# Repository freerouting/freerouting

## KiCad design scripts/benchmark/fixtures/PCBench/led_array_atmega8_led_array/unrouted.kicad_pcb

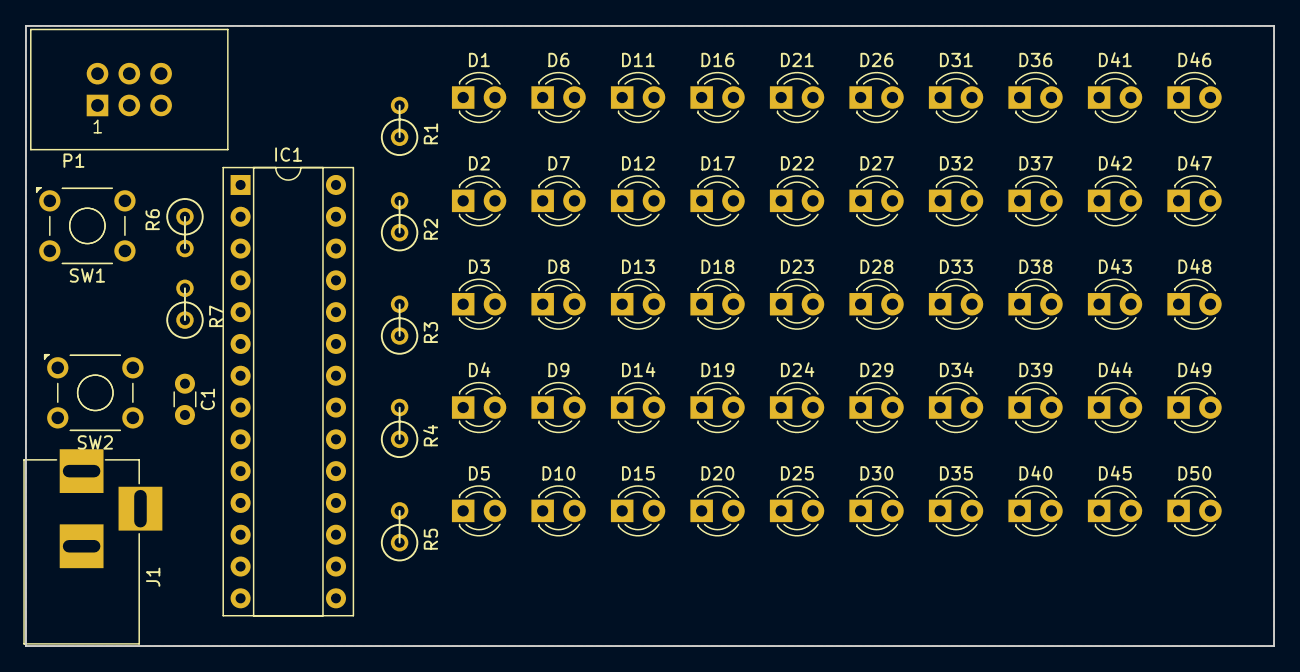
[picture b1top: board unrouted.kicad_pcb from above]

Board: 2 copper layers, 99.7 x 49.5 mm, 63 parts (0 on the bottom side), 25 nets, no tracks yet.

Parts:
C1: 0.1uF; C_Disc_D3.0mm_W1.6mm_P2.50mm
D1, D2, D3, D4, D5, D6, D7, D8, D9, D10, D11, D12, D13, D14, D15, D16, D17, D18, D19, D20, D21, D22, D23, D24, D25, D26, D27, D28, D29, D30, D31, D32, D33, D34, D35, D36, D37, D38, D39, D40, D41, D42, D43, D44, D45, D46, D47, D48, D49, D50: LED; LED_D3.0mm
IC1: ATMEGA8-P; DIP-28_W7.62mm_Socket
J1: BARREL_JACK
P1: ICSP; IDC_Header_Straight_6pins
R1, R2, R3, R4, R5: 220; R1
R6, R7: 1k; R1
SW1: next; SW_TH_Tactile_Omron_B3F-10xx
SW2: prev; SW_TH_Tactile_Omron_B3F-10xx

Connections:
+5V: C1.1, IC1.7, J1.1, P1.2, SW1.1, SW1.3, SW2.1, SW2.3
GND: C1.2, IC1.8, J1.2, J1.3, P1.6, R6.1, R7.1
MISO: D11.1, D12.1, D13.1, D14.1, D15.1, IC1.18, P1.1
MOSI: D16.1, D17.1, D18.1, D19.1, D20.1, IC1.17, P1.4
unnamed: D1.2, D6.2, D11.2, D16.2, D21.2, D26.2, D31.2, D36.2, D41.2, D46.2, R1.2
unnamed: D5.2, D10.2, D15.2, D20.2, D25.2, D30.2, D35.2, D40.2, D45.2, D50.2, R5.2
unnamed: D2.2, D7.2, D12.2, D17.2, D22.2, D27.2, D32.2, D37.2, D42.2, D47.2, R2.2
unnamed: D3.2, D8.2, D13.2, D18.2, D23.2, D28.2, D33.2, D38.2, D43.2, D48.2, R3.2
unnamed: D4.2, D9.2, D14.2, D19.2, D24.2, D29.2, D34.2, D39.2, D44.2, D49.2, R4.2
RST: IC1.1, P1.5
SCK: D6.1, D7.1, D8.1, D9.1, D10.1, IC1.19, P1.3
back: IC1.5, R7.2, SW2.2, SW2.4
col1: D1.1, D2.1, D3.1, D4.1, D5.1, IC1.23
col5: D21.1, D22.1, D23.1, D24.1, D25.1, IC1.16
col6: D26.1, D27.1, D28.1, D29.1, D30.1, IC1.15
col7: D31.1, D32.1, D33.1, D34.1, D35.1, IC1.14
col8: D36.1, D37.1, D38.1, D39.1, D40.1, IC1.11
col9: D41.1, D42.1, D43.1, D44.1, D45.1, IC1.12
col10: D46.1, D47.1, D48.1, D49.1, D50.1, IC1.13
forward: IC1.4, R6.2, SW1.2, SW1.4
row1: IC1.28, R1.1
row2: IC1.27, R2.1
row3: IC1.26, R3.1
row4: IC1.25, R4.1
row5: IC1.24, R5.1

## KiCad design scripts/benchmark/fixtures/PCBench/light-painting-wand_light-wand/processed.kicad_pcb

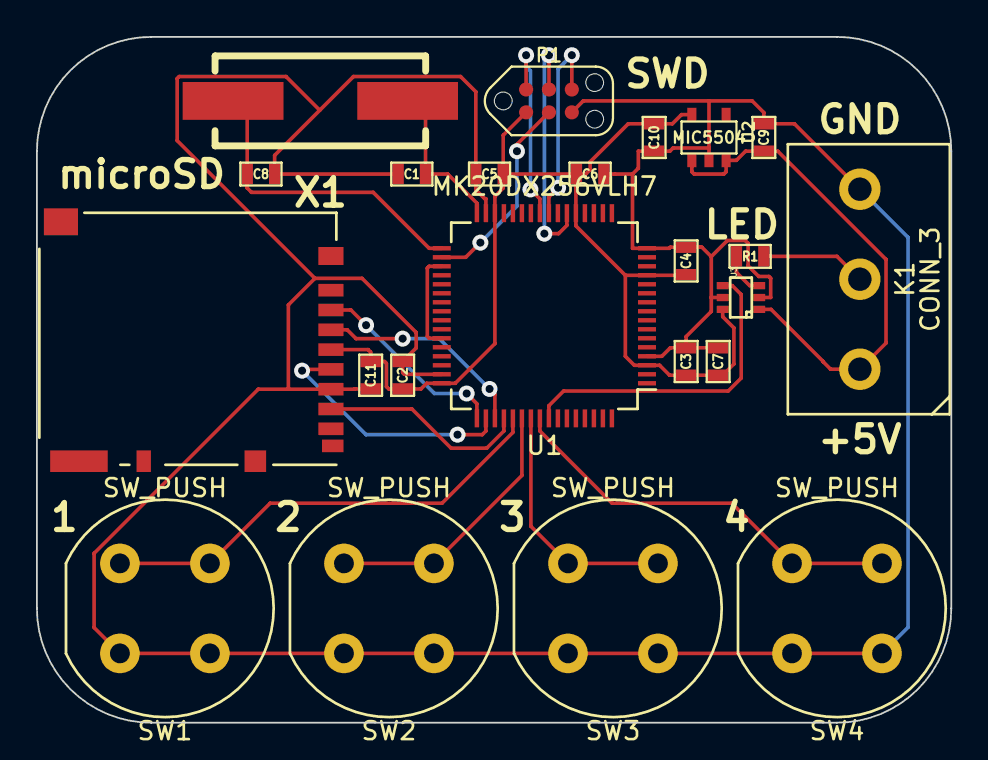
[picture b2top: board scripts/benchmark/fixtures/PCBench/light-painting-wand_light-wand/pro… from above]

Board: 2 copper layers, 50.8 x 38.1 mm, 24 parts (1 on the bottom side), 21 nets.

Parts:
C1, C8: 27pF; SMD-0603
C2, C3, C4, C5, C6, C11: 0.1uF; SMD-0603
C7: 2.2uF; SMD-0603
C9, C10: 1uF; SMD-0603
K1: CONN_3; 1935174
P1: TC2030-CTX; TC2030-NL_SMALL
R1: 68; SMD-0603
SW1, SW2, SW3, SW4: SW_PUSH; D6_SWITCH
SYM: Symbol_OSHW-Logo_SilkScreen_07Jul2012; Symbol_OSHW-Logo_SilkScreen
U1: MK20DX256VLH7; LQFP-64_10x10mm_Pitch0.5mm
U2: MIC5504; SOT-23-5
U3: SN74LVC1T45; sc70-6
U4: MICROSD_SOCKET; DM3BT
X1: 16MHz; Crystal_HC49-SD_SMD

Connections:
+3.3V: C2.1, C3.1, C4.1, C5.1, C6.1, C7.1, C10.1, C11.1, P1.1, U1.3, U1.13, U1.21, U1.30, U1.48, U2.5, U3.6, U4.4
+5V: C9.1, K1.1, U2.1, U2.3, U3.1
/BTN1: SW1.1, U1.53
/BTN2: SW2.1, U1.54
/BTN3: SW3.1, U1.55
/BTN4: SW4.1, U1.56
/CS: U1.49, U4.2
/MISO: U1.52, U4.7
/MOSI: U1.51, U4.3
/RESET: P1.3, U1.34
/SCK: U1.50, U4.5
/SWCLK: P1.4, U1.22
/SWDIO: P1.2, U1.25
/SWO: P1.6, U1.24
/WS2812: R1.2, U3.3
/WS2812_L: U1.57, U3.4
GND: C1.2, C2.2, C3.2, C4.2, C5.2, C6.2, C7.2, C8.2, C9.2, C10.2, C11.2, K1.3, P1.5, SW1.2, SW2.2, SW3.2, SW4.2, U1.4, U1.16, U1.31, U1.47, U2.2, U3.2, U3.5, U4.6
unnamed: C1.1, U1.32, X1.1
unnamed: C8.1, U1.33, X1.2
unnamed: K1.2, R1.1
unnamed: U1.35, U1.43

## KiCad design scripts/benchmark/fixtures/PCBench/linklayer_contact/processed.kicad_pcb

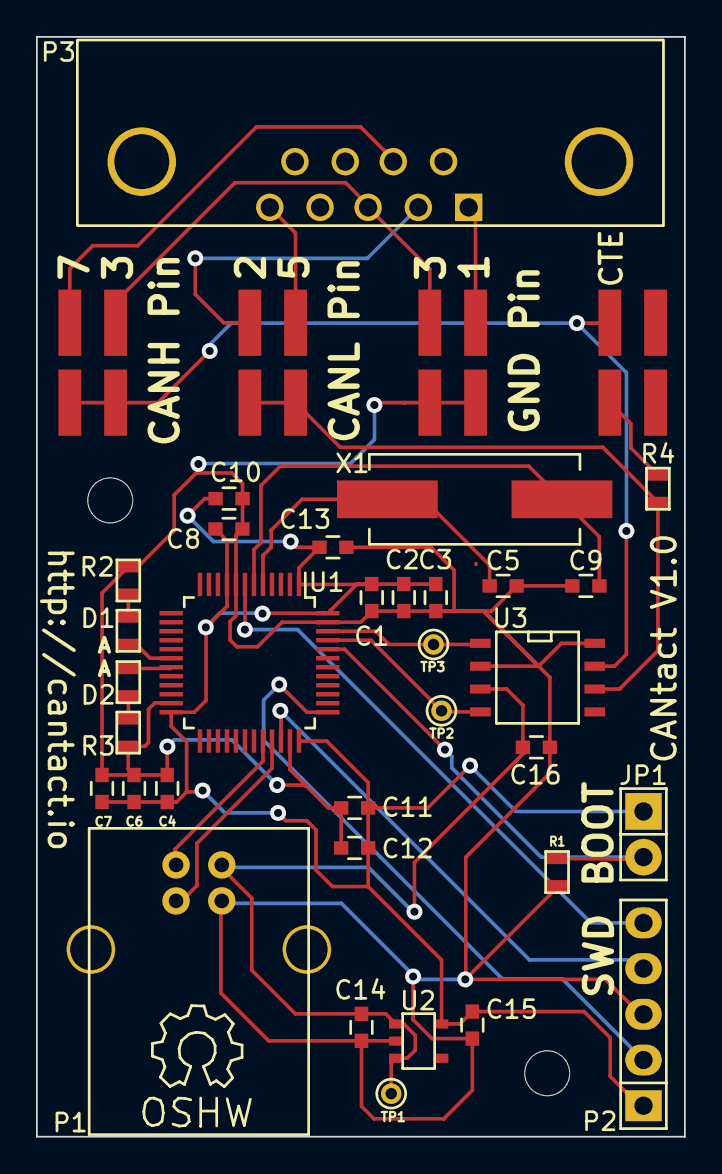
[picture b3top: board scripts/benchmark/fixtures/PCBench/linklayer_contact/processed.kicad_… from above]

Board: 2 copper layers, 36.0 x 61.1 mm, 40 parts (0 on the bottom side), 25 nets.

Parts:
C1, C2, C4, C6, C11, C13, C16: 0.1uF; C_0603
C3, C7, C12: 4.7uF; C_0603
C5, C9: 18pF; C_0603
C8: 10nF; C_0603
C10, C14, C15: 1uF; C_0603
D1, D2: LED; SMD-0603
JP1: Boot Mode; Pin_Header_Straight_1x02
JP2: Term Enable; 0015912040
JP3: CANH Select; 0015912040
JP4: CANL Select; 0015912040
JP5: GND Select; 0015912040
Noname_1, Noname_2: VAL**; MountingHole_2-5mm
P1: USB; USB_B
P2: SWD; Pin_Header_Straight_1x05
P3: DB9; DB9MC
R1: 510; SMD-0603
R2, R3: R; SMD-0603
R4: 120; SMD-0603
SYM: Symbol_OSHW-Logo_SilkScreen_07Jul2012; Symbol_OSHW-Logo_SilkScreen
TP1, TP2, TP3: TST; PINTST
U1: STM32F042C6T6; LQFP-48_7x7mm_Pitch0.5mm
U2: AAT3221; SOT-23-5
U3: MCP2551-I/SN; SOIC-8-N
X1: 16 MHz; Crystal_HC49-SD_SMD

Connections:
+3.3V: C1.1, C2.1, C3.1, C4.1, C6.1, C7.1, C8.1, C10.1, C11.1, C12.1, C13.1, C15.1, JP1.1, P2.1, U1.1, U1.9, U1.24, U1.36, U1.48, U2.5
+5V: C14.1, C16.2, P1.1, TP1.1, U2.1, U2.3, U3.3
/CAN_RX: TP2.1, U1.45, U3.4
/CAN_TX: TP3.1, U1.46, U3.1
/DB9_1: JP5.4, P3.1
/DB9_2: JP4.2, P3.2
/DB9_3: JP3.4, JP5.2, P3.3
/DB9_5: JP4.4, P3.5
/DB9_7: JP3.2, P3.7
/NRST: P2.5, U1.7
/SWCLK: P2.2, U1.37
/SWDIO: P2.4, U1.34
/USB_DM: P1.2, U1.32
/USB_DP: P1.3, U1.33
GND: C1.2, C2.2, C3.2, C4.2, C5.2, C6.2, C7.2, C8.2, C9.2, C10.2, C11.2, C12.2, C13.2, C14.2, C15.2, C16.1, JP5.1, JP5.3, P1.4, P2.3, R1.2, R2.1, R3.1, U1.8, U1.23, U1.35, U1.47, U2.2, U3.2, U3.8
unnamed: C5.1, U1.5, X1.1
unnamed: C9.1, U1.6, X1.2
unnamed: D1.1, U1.18
unnamed: D1.2, R2.2
unnamed: D2.1, U1.19
unnamed: D2.2, R3.2
unnamed: JP1.2, R1.1, U1.44
unnamed: JP2.1, R4.2
unnamed: JP2.2, JP3.1, JP3.3, U3.7
unnamed: JP4.1, JP4.3, R4.1, U3.6

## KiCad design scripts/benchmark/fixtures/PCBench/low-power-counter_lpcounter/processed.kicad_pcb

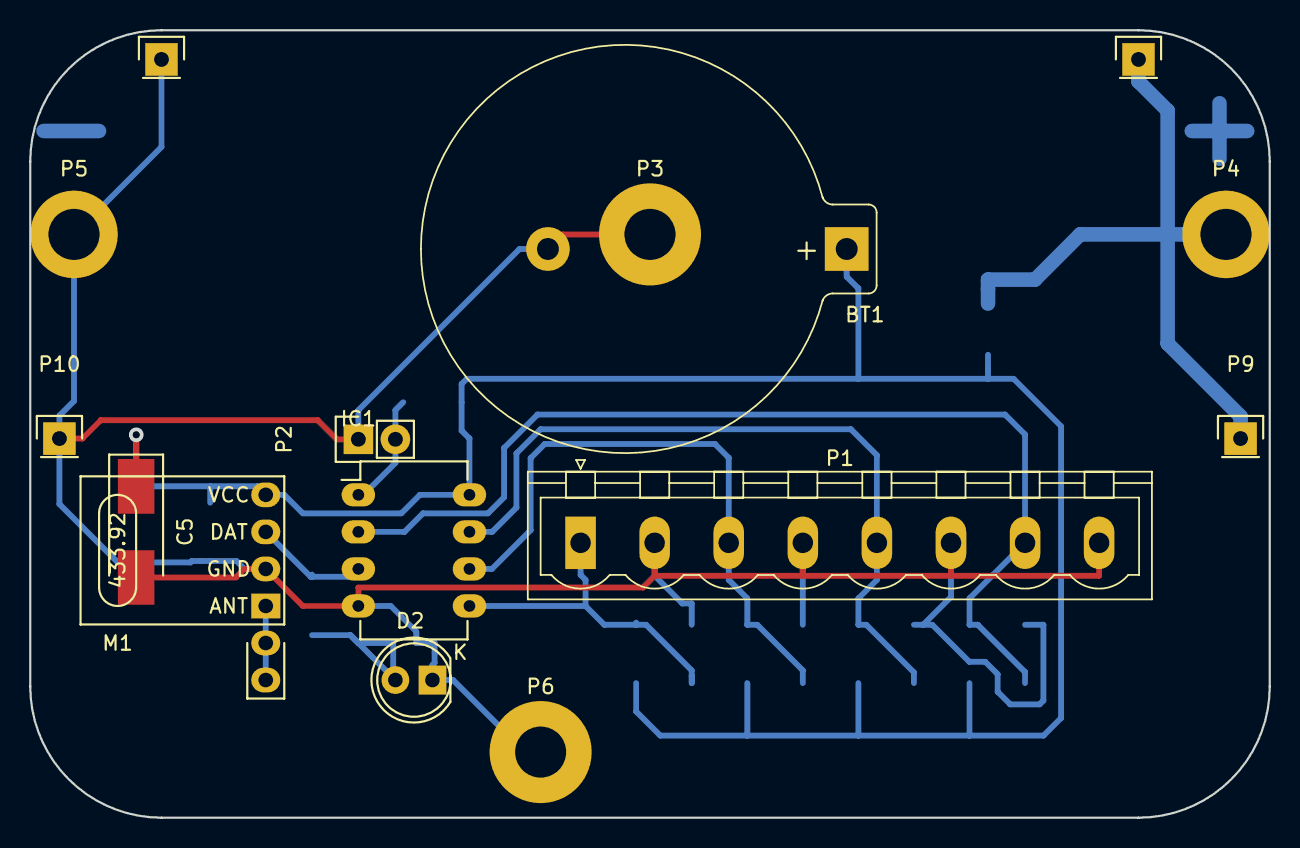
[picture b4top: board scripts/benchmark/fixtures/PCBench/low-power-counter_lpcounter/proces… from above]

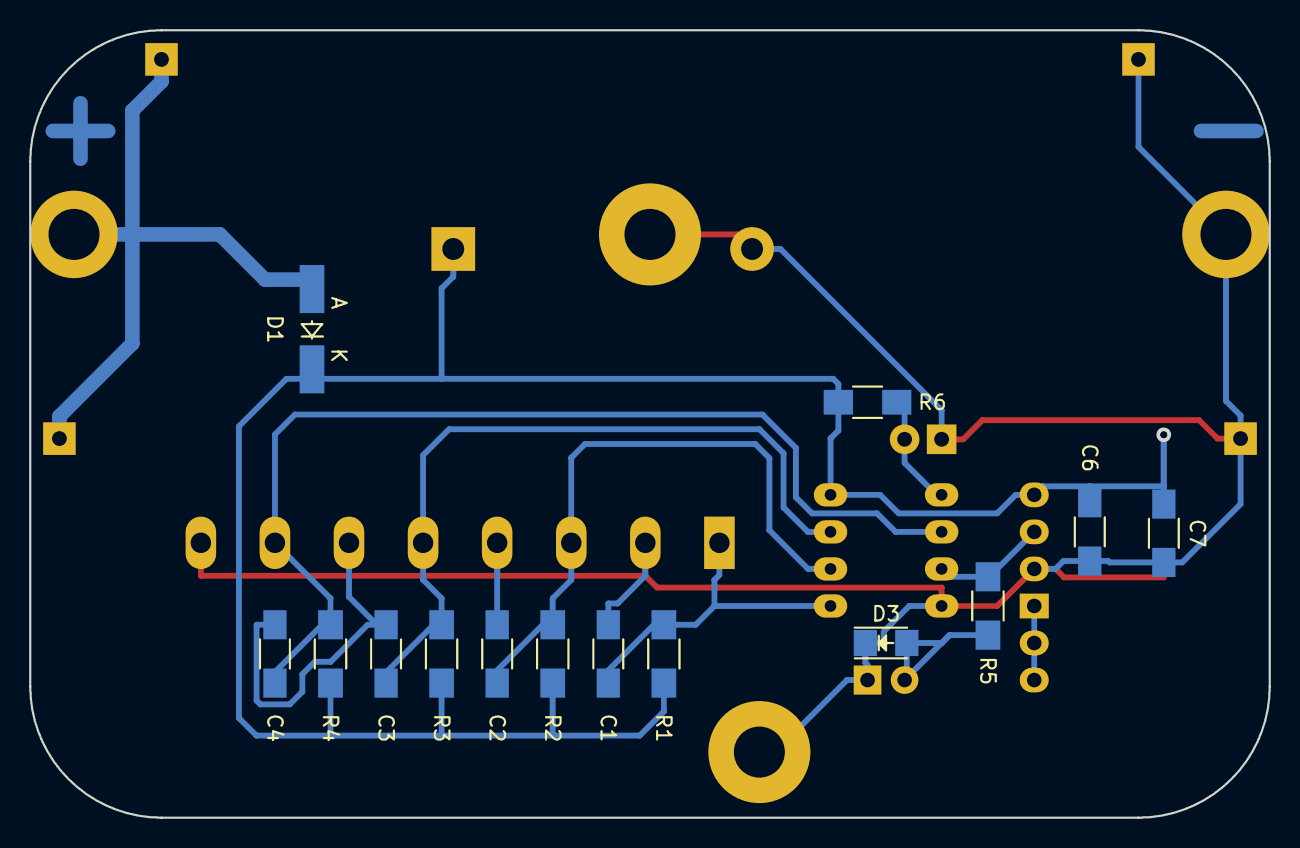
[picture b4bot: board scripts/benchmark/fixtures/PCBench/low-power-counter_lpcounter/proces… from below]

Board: 2 copper layers, 85.0 x 54.0 mm, 29 parts (14 on the bottom side), 10 nets.

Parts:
BT1: CR2032; Keystone_106_1x20mm-CoinCell
C1, C2, C3, C4, C6, C7: 100nF; C_1206_HandSoldering
C5: 4.7uF; Tantalum_Case-U_EIA-6032-15_Hand
D1: 1N4148; MiniMELF_Handsoldering
D2: ORANGE; LED-5MM
D3: ORANGE; LED_1206
IC1: ATTINY85V-P; DIP-8_W7.62mm_LongPads
M1: SYN115
P1: CONN_01X08; PhoenixContact_MSTBVA-G_08x5.08mm_Vertical
P2: CONN_02X01; Pin_Header_Straight_1x02
P3, P4, P5, P6: Hole_3.5mm; MountingHole_3.5mm_Pad
P7, P9: BAT+; Pin_Header_Straight_1x01
P8, P10: BAT-; Pin_Header_Straight_1x01
R1, R2, R3, R4: 1M; R_1206_HandSoldering
R5: 1k; R_1206_HandSoldering
R6: 10k; R_1206_HandSoldering

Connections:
+3V3: BT1.1, C5.1, C6.1, C7.1, D1.1, IC1.8, M1.4, R1.1, R2.1, R3.1, R4.1, R6.1
/IN0: C1.1, IC1.5, P1.1, R1.2
/IN1: C2.1, IC1.6, P1.3, R2.2
/IN2: C3.1, IC1.7, P1.5, R3.2
/IN3: C4.1, IC1.2, P1.7, R4.2
/LED: D2.2, D3.2, R5.1
/OUT: IC1.3, M1.3, R5.2
/RESETn: IC1.1, P2.2, R6.2
/VBAT: D1.2, P4.1, P7.1, P9.1
GND: BT1.2, C1.2, C2.2, C3.2, C4.2, C5.2, C6.2, C7.2, D2.1, D3.1, IC1.4, M1.2, P1.2, P1.4, P1.6, P1.8, P2.1, P3.1, P5.1, P6.1, P8.1, P10.1

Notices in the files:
scripts/benchmark/fixtures/PCBench/light-painting-wand_light-wand/processed.kicad_pcb:
CC BY 4.0
